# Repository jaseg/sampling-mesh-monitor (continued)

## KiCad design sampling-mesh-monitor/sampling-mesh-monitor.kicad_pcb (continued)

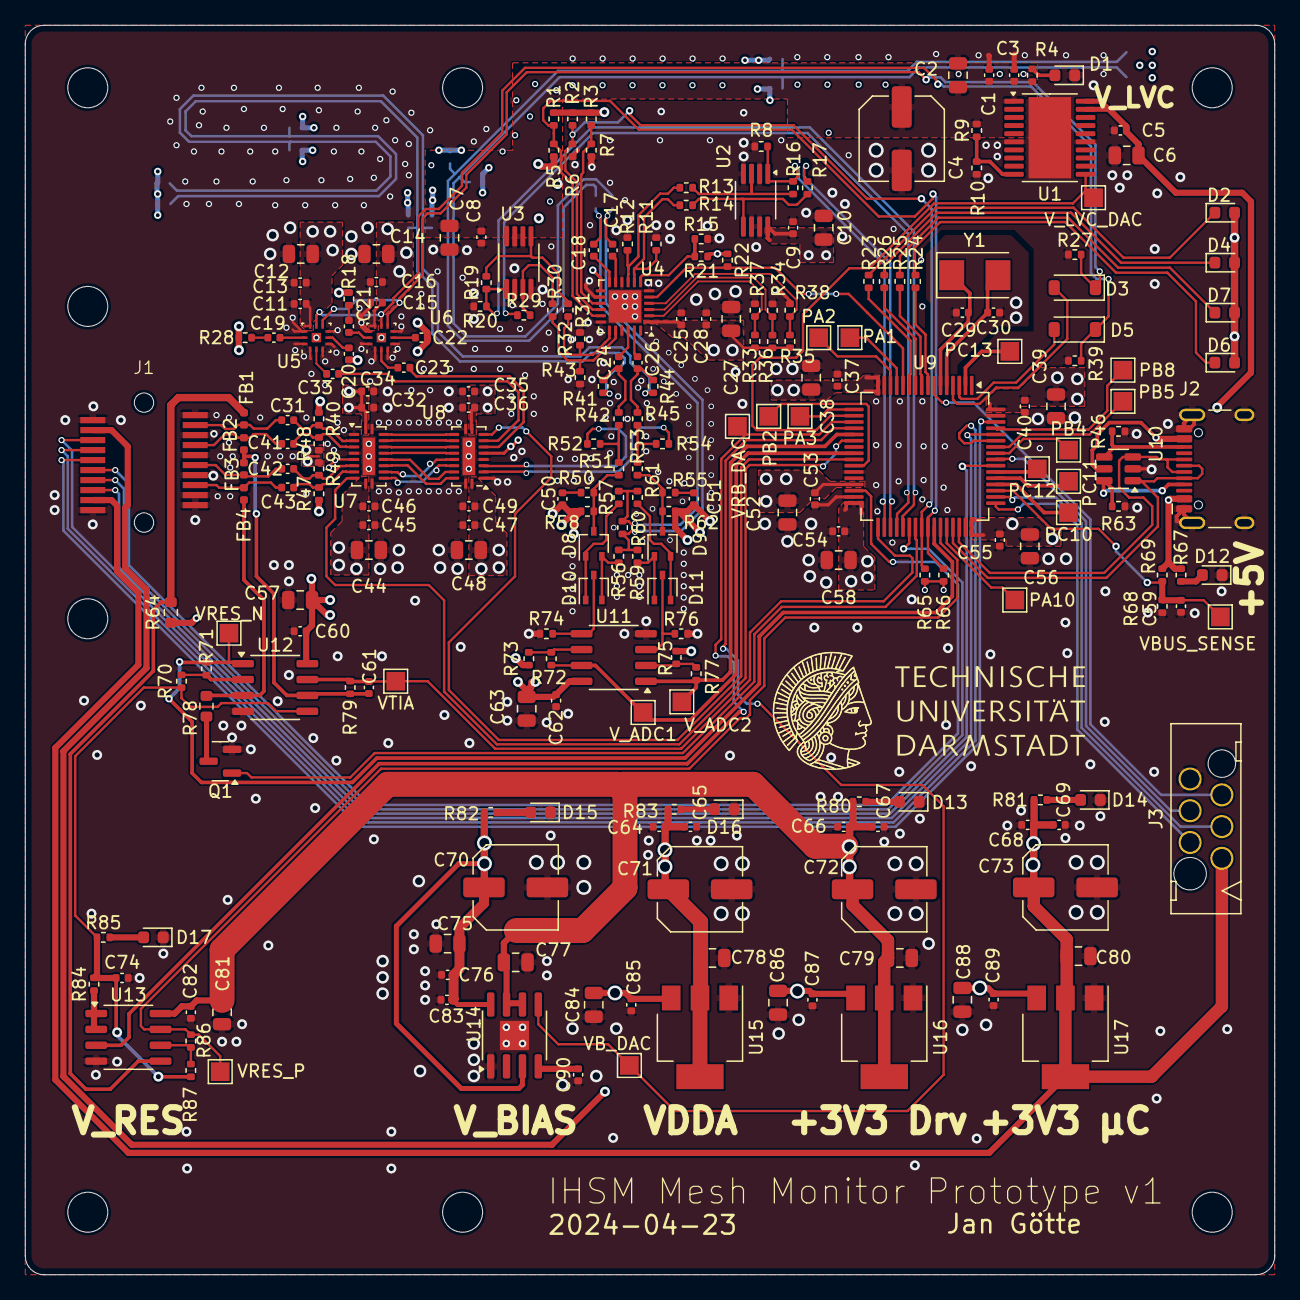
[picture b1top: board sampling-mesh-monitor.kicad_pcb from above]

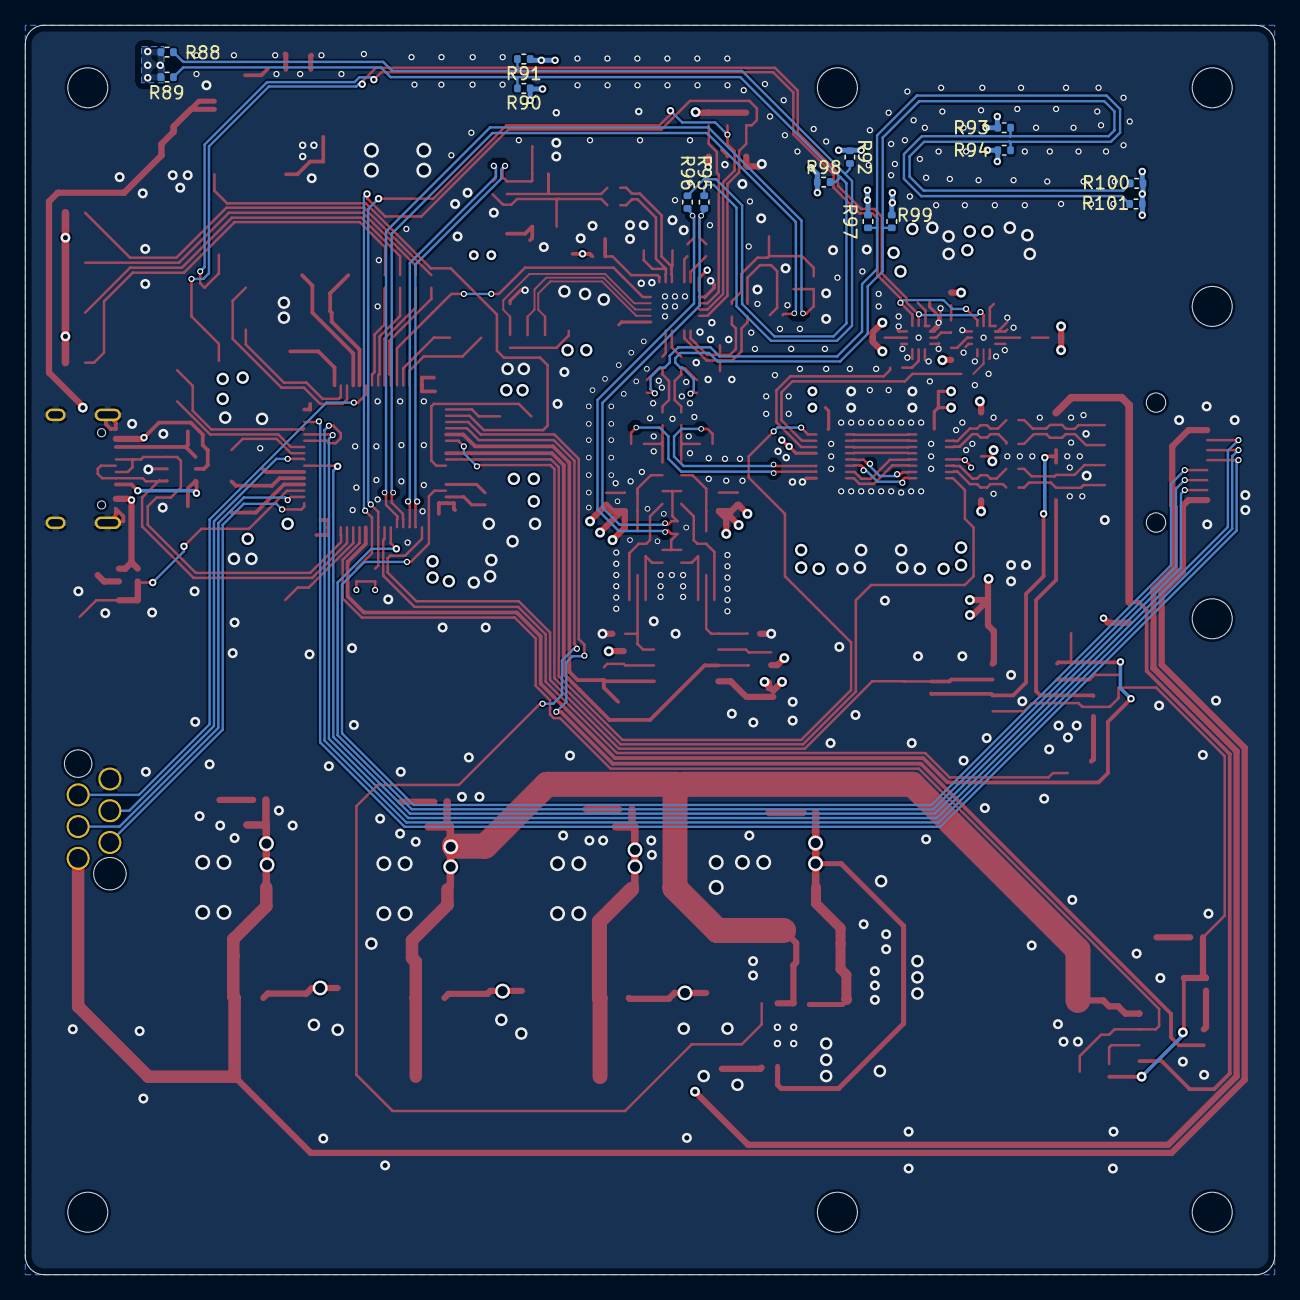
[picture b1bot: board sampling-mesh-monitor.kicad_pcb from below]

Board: 15 copper layers, 100.0 x 100.0 mm, 264 parts (14 on the bottom side), 150 nets.

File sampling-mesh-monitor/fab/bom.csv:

Comment,Designator,Footprint,LCSC
22k,"R68,R73,R75",Resistor_SMD:R_0402_1005Metric,C25768
47u,"C4,C70,C71,C72,C73",Capacitor_SMD:C_Elec_6.3x7.7,C88810
10n,"C3,C11,C15,C17,C18,C19,C20,C21,C22,C23,C24,C25,C26,C31,C32,C33,C36,C41,C42,C43,C46,C49,C65,C67,C69,C74,C76,C90",Capacitor_SMD:C_0402_1005Metric,C15195 
1k,"R4,R23,R24,R25,R26,R67,R80,R81,R82,R83,R85,R87",Resistor_SMD:R_0402_1005Metric,C11702 
45,"R18,R28,R58,R62",Resistor_SMD:R_0402_1005Metric,C327342
3k3,"R27,R39,R65,R66",Resistor_SMD:R_0402_1005Metric,C25890
1u,"C2,C6,C7,C10,C12,C14,C27,C38,C39,C44,C48,C52,C56,C57,C58,C63,C75,C77,C78,C79,C80,C81,C84,C86,C88",Capacitor_SMD:C_0805_2012Metric,C28323
0,"R9,R13,R14,R30,R31,R41,R44,R95,R96",Resistor_SMD:R_0402_1005Metric,C17168 
USBLC6-4SC6,U10,Package_TO_SOT_SMD:SOT-23-6,C558419
AO3400A,Q1,Package_TO_SOT_SMD:SOT-23,C20917
10k,"R40,R47,R48,R49,R70",Resistor_SMD:R_0402_1005Metric,C2654005
100n,"C1,C5,C8,C9,C13,C16,C28,C34,C35,C37,C40,C45,C47,C53,C54,C55,C59,C60,C62,C64,C66,C68,C82,C83,C85,C87,C89",Capacitor_SMD:C_0402_1005Metric,C307331
75,"R8,R11,R12,R20,R32,R43",Resistor_SMD:R_0402_1005Metric,C25133
BLM15HD102SN1D,"FB1,FB2,FB3,FB4",Inductor_SMD:L_0402_1005Metric,C21516
91,"R56,R57,R59,R61",Resistor_SMD:R_0402_1005Metric,C4071412
1N4148W,"D3,D5",Diode_SMD:D_SOD-123,C81598
47k,"R71,R72,R77,R86",Resistor_SMD:R_0402_1005Metric,C25792
PTN36241B,U4,Package_DFN_QFN:QFN-24-1EP_4x4mm_P0.5mm_EP2.6x2.6mm,C2675242
0603 white,"D1,D2,D4,D6,D7,D12,D13,D14,D15,D16,D17",LED_SMD:LED_0603_1608Metric,C2290
SKYA21003,"U5,U6",footprints:QFN-12_EP_2x2_Pitch0.5mm,C141440
74LVC2G157,"U2,U3",Package_SO:MSOP-8_3x3mm_P0.65mm,C78048 
30,"R42,R45,R51,R52,R53,R54",Resistor_SMD:R_0402_1005Metric,C138007
100,R84,Resistor_SMD:R_0402_1005Metric,C25076
20p,"C29,C30",Capacitor_SMD:C_0402_1005Metric,C1554
OPA1656,"U11,U12,U13",Package_SO:SO-8_3.9x4.9mm_P1.27mm,C1849431
BAT17-04W,"D8,D9,D10,D11",Package_TO_SOT_SMD:SOT-323_SC-70,C503474
AMS1117-3.3,"U15,U16,U17",Package_TO_SOT_SMD:SOT-223-3_TabPin2,C6186
5k1,"R46,R63",Resistor_SMD:R_0402_1005Metric,C25905
47,"R64,R78",Resistor_SMD:R_0603_1608Metric,C23182
TMUXHS4212,"U7,U8",Package_DFN_QFN:DHVQFN-20-1EP_2.5x4.5mm_P0.5mm_EP1x3mm,C3656912
1M,"R74,R76,R79",Resistor_SMD:R_0402_1005Metric,C138033
USB_C_Receptacle_USB2.0,J2,Connector_USB:USB_C_Receptacle_HCTL_HC-TYPE-C-16P-01A,C2988369
8MHz/20p,Y1,Crystal:Crystal_SMD_5032-2Pin_5.0x3.2mm,C115962
SFP+,J1,footprints:HCTL_HC-SFP-20P_C2897291,C2897291
100k,R69,Resistor_SMD:R_0402_1005Metric,C25741
STM32G474RBTx,U9,Package_QFP:LQFP-64_10x10mm_P0.5mm,C529413
TPS7B4253QPWPRQ1,U1,Package_SO:HTSSOP-20-1EP_4.4x6.5mm_P0.65mm_EP3.4x6.5mm_Mask2.4x3.7mm,C2879376
LP2998,U14,footprints:SOIC-8-1EP_3.9x4.9mm_P1.27mm_EP2.34x2.34mm,C181400

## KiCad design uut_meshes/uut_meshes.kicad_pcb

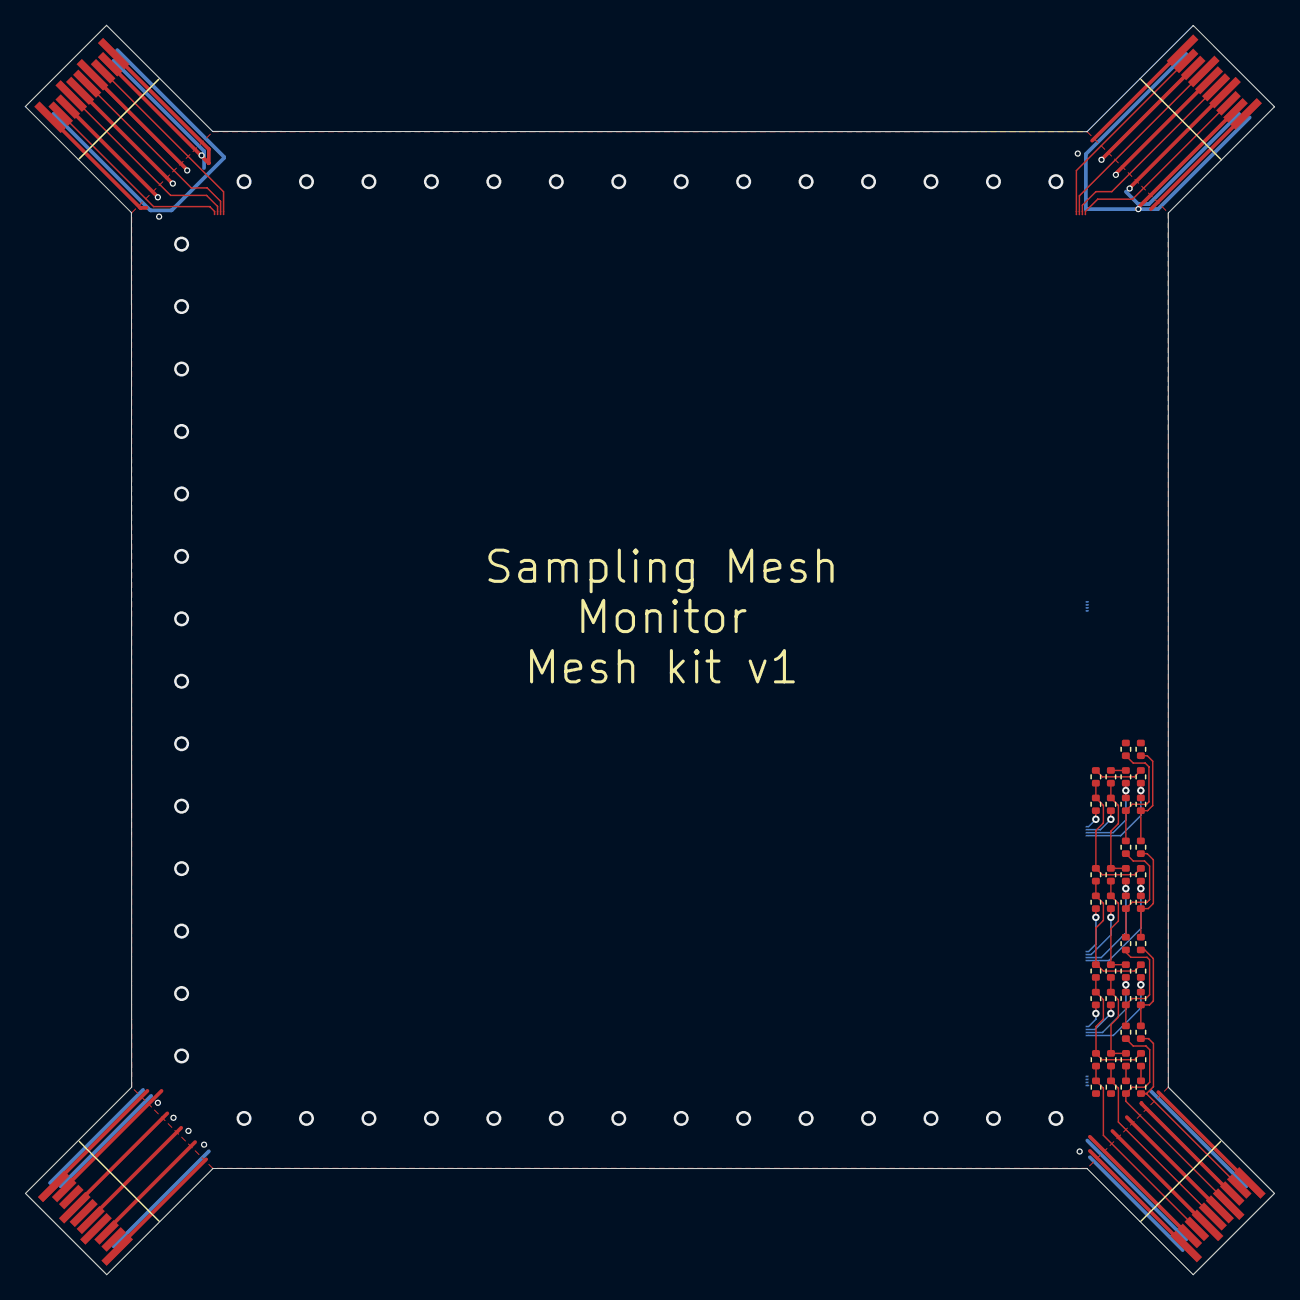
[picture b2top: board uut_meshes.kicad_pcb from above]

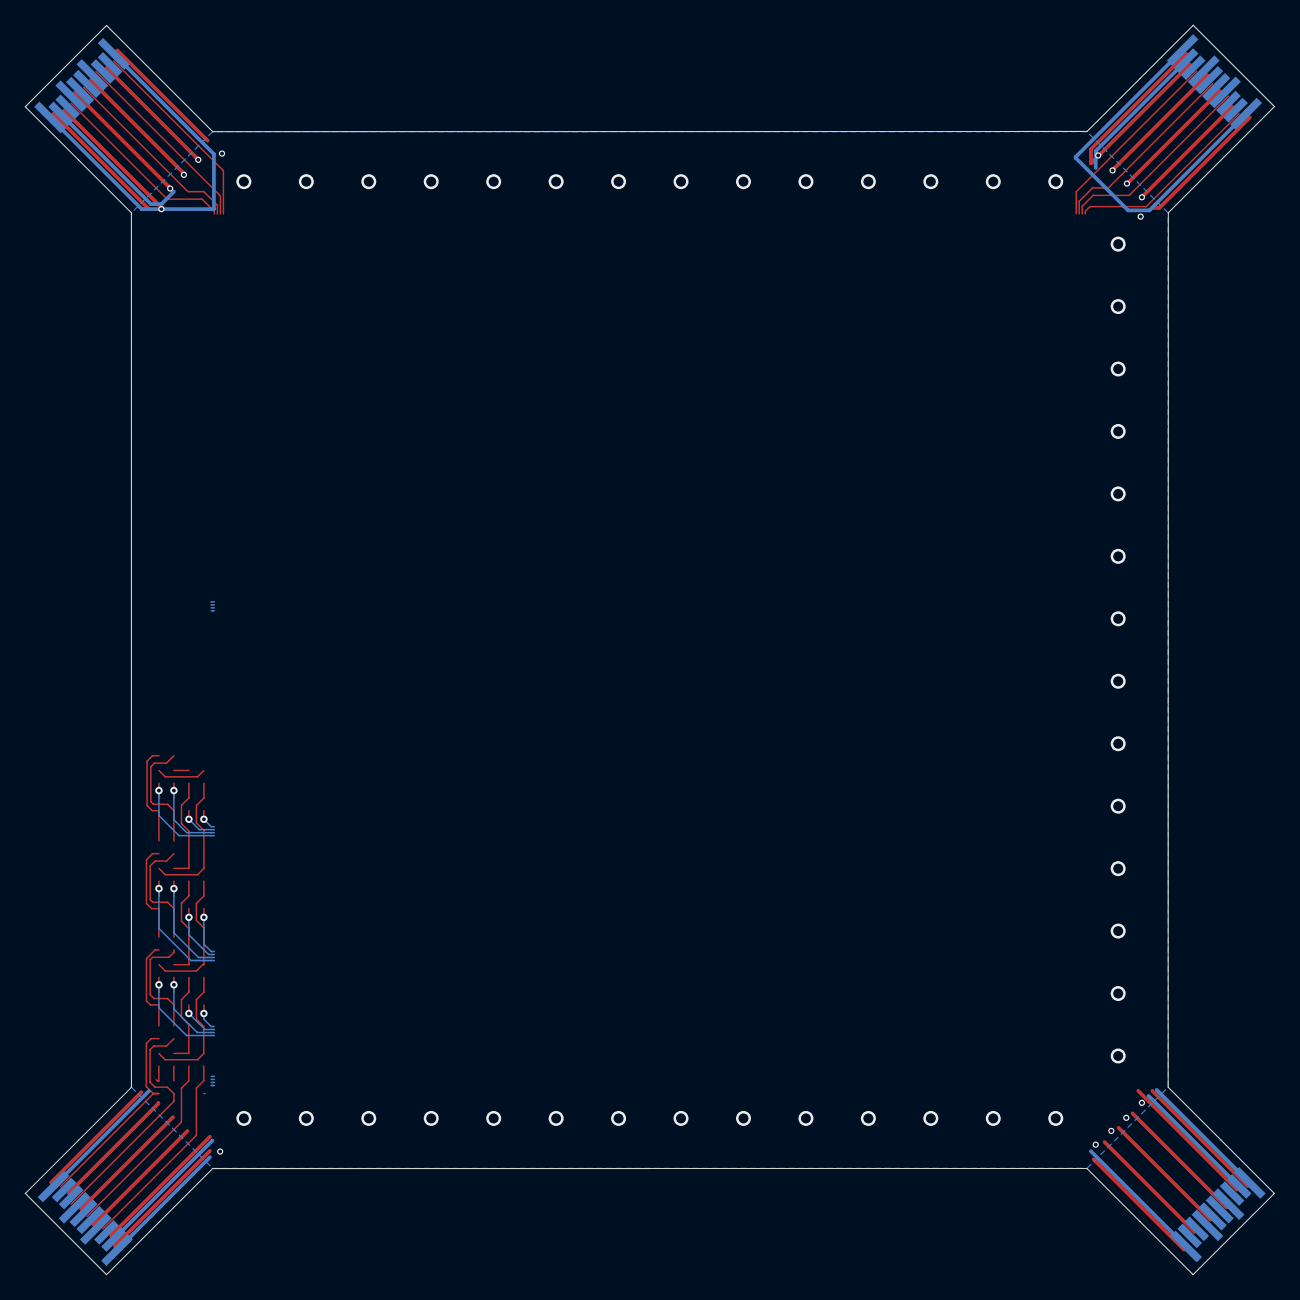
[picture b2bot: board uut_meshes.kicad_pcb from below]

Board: 4 copper layers, 100.0 x 100.0 mm, 51 parts (5 on the bottom side), 57 nets.

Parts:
J1, J2, J3, J4: Conn_02x10_Counter_Clockwise; sfp_edge_connector_male
J5, J6, J7, J9, J10, J11, J12: Conn_02x04_Top_Bottom; MeshAnchor_2W_T0.120mm_S0.120mm
R1, R2, R3, R4, R5, R6, R7, R8, R9, R10, R11, R12, R13, R14, R15, R16, R17, R18, R19, R20, R21, R22, R23, R24, R25, R26, R27, R28, R29, R30, R31, R32, R33, R34, R35, R36, R37, R38, R39, R40: 0; R_0402_1005Metric

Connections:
GND: J1.1, J1.9, J1.10, J1.11, J1.12, J1.14, J1.16, J1.18, J1.20, J2.1, J2.9, J2.10, J2.11, J2.12, J2.14, J2.16, J2.18, J2.20, J3.1, J3.9, J3.10, J3.11, J3.12, J3.14, J3.16, J3.18, J3.20, J4.1, J4.9, J4.10, J4.11, J4.12, J4.14, J4.16, J4.18, J4.20
unnamed: J1.13, J6.1
unnamed: J1.15, J6.2
unnamed: J1.17, J6.3
unnamed: J1.19, J6.4
unnamed: J2.13, R2.2, R5.2
unnamed: J2.15, R1.2, R6.2
unnamed: J2.17, R3.2, R10.2
unnamed: J2.19, R4.2, R9.2
unnamed: J4.13, J5.1
unnamed: J4.15, J5.2
unnamed: J4.17, J5.3
unnamed: J4.19, J5.4
unnamed: J5.5, J5.8
unnamed: J5.6, J5.7
unnamed: J6.5, J6.8
unnamed: J6.6, J6.7
unnamed: J7.1, R2.1
unnamed: J7.2, R1.1
unnamed: J7.3, R3.1, R8.2
unnamed: J7.4, R4.1, R7.2
unnamed: J7.5, J7.8
unnamed: J7.6, J7.7
unnamed: J9.1, R11.1
unnamed: J9.2, R12.1
unnamed: J9.3, R13.1, R19.2
unnamed: J9.4, R14.1, R20.2
unnamed: J9.5, J9.8
unnamed: J9.6, J9.7
unnamed: J10.1, R21.1
unnamed: J10.2, R22.1
unnamed: J10.3, R23.1, R29.2
unnamed: J10.4, R24.1, R30.2
unnamed: J10.5, J10.8
unnamed: J10.6, J10.7
unnamed: J11.1, R31.1
unnamed: J11.2, R32.1
unnamed: J11.3, R33.1, R39.2
unnamed: J11.4, R34.1, R40.2
unnamed: J11.5, J11.8
unnamed: J11.6, J11.7
unnamed: J12.5, J12.8
unnamed: J12.6, J12.7
unnamed: R10.1, R13.2, R16.2
unnamed: R5.1, R7.1, R11.2, R18.2
unnamed: R6.1, R8.1, R12.2, R17.2
unnamed: R9.1, R14.2, R15.2
unnamed: R15.1, R24.2, R25.2
unnamed: R16.1, R23.2, R26.2
unnamed: R17.1, R19.1, R22.2, R27.2
unnamed: R18.1, R20.1, R21.2, R28.2
unnamed: R25.1, R34.2, R35.2
unnamed: R26.1, R33.2, R36.2
unnamed: R27.1, R29.1, R32.2, R37.2
unnamed: R28.1, R30.1, R31.2, R38.2
unnamed: R37.1, R39.1
unnamed: R38.1, R40.1

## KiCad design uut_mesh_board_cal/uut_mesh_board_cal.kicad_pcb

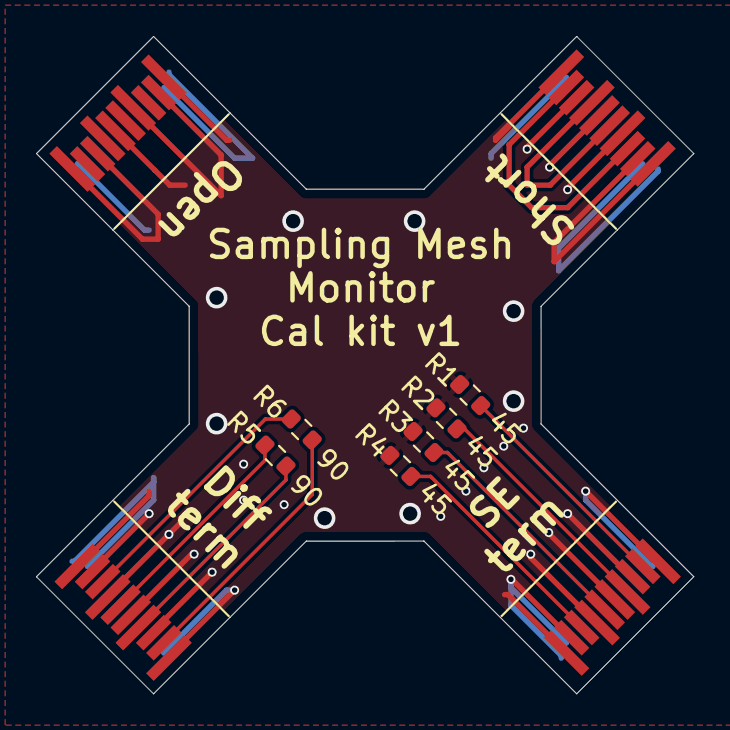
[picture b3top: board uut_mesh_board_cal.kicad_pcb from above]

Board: 2 copper layers, 36.5 x 36.5 mm, 11 parts (1 on the bottom side), 11 nets.

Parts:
J1, J2, J3, J4: Conn_02x10_Counter_Clockwise; sfp_edge_connector_male
R1, R2, R3, R4: 45; R_0603_1608Metric
R5, R6: 90; R_0603_1608Metric
logo_tu_darmstadt_15.0mm: G*****; logo_tu_darmstadt_15.0mm

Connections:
GND: J1.1, J1.9, J1.10, J1.11, J1.12, J1.14, J1.16, J1.18, J1.20, J2.1, J2.9, J2.10, J2.11, J2.12, J2.14, J2.16, J2.18, J2.20, J3.1, J3.9, J3.10, J3.11, J3.12, J3.14, J3.16, J3.18, J3.20, J4.1, J4.9, J4.10, J4.11, J4.12, J4.14, J4.16, J4.18, J4.20, R1.1, R2.1, R3.1, R4.1
unnamed: J1.13, J1.19
unnamed: J1.15, J1.17
unnamed: J2.13, R4.2
unnamed: J2.15, R3.2
unnamed: J2.17, R2.2
unnamed: J2.19, R1.2
unnamed: J3.13, R6.1
unnamed: J3.15, R5.1
unnamed: J3.17, R5.2
unnamed: J3.19, R6.2

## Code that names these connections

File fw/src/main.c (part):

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                    AFRH(14, 0) | /* SWCLK */
                    AFRH(10, 13); /* HRTIM1 Channel B1 */
    GPIOA->OSPEEDR = 0xffffffff;
    GPIOA->BRR = (1<<0); /* Clear DRV_CEN */

    /* GPIOB: 
     *  0 -  V_ADC1 -> ADC1 CH15
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
    GPIOB->MODER = ANALOG(0) | OUT(1) | IN(2) | AF(3) | AF(4) | IN(5) | IN(6) | IN(7) | OUT(8) | IN(9) | IN(10) |
        ANALOG(11) | AF(12) | IN(13) | IN(14) | AF(15);
    GPIOB->AFR[0] = AFRL( 3, 0)  | /* SWO */
                    AFRL( 4, 1);   /* TIM16 CH1 */
    GPIOB->AFR[1] = AFRH(12, 13) | /* HRTIM1 Channel C1 */
                    AFRH(13, 13) | /* HRTIM1 Channel C2 */
                    AFRH(14, 13) | /* HRTIM1 Channel D1 */
                    AFRH(15, 13);  /* HRTIM1 Channel D2 */
    GPIOB->OSPEEDR = 0xffffffff;
    GPIOB->BSRR = (1<<1); /* Set MESH_FLIP_N, leave MESH_FLIP reset below. These two must be complementary. */

    /* GPIOC:
     *  0 -  LED1
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
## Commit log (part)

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2024-04-24 Initial commmit
2024-04-24 PCB almost finished
2024-04-24 Reannotate reference designators by PCB location
2024-04-24 Add cal kit UUT
2024-04-24 uut/cal kit: Add version number
2024-04-24 uut/mesh: Add mesh uut
2024-04-25 Mesh test board WIP
2024-04-25 meshes WIP
2024-07-22 Add fw skeleton
2024-07-22 redriver bringup WIP
2024-11-18 Get the ADCs converting
2024-11-19 Add live measurement plot
2024-11-20 Add clock documentation
2024-11-20 We get first, very rough sampled measurements
2024-11-20 Speed up display
2024-11-22 straighten out HRTIM triggering
2024-11-22 Improved channel 1 sampling
2024-11-22 I2C wasn't working, with pin-strapped driver config we now get some *very* spicy edges it seems
    This commit also scales the web UI plots' X axis in ns and Y axis in V.
2024-11-23 Add todos to board schematic
2024-11-23 Move stimulus instead of sampling pulse, eliminates ADC alignment issue
    The ADC can only trigger on whole clock pulses, so when we move the
    sampling pulse in fractional increments, the relative alignment of the
    ADC's sampling phase w.r.t. sampling pulse moves around +/-0.5 clock
    periods. Since our opamps ring a bit, that leads to an artifact in the
    measurements with a period of 32 samples (one whole clock pulse). Moving
    the stimulus pulse instead fixes this issue, as now the alignment
2024-11-23 Decrease oversampling to increase update rate
2024-11-23 Something weird is happening with the hrtim master period
    This new value gives much cleaner curves. I suspect that either we have
    some issue with ADC sampling not being precise due to clock domain
    crossings, or this is just interference and the new period hits a sweet
    spot that is coherent with this interference.
2024-11-25 Extend remote control both ways
2024-11-25 make sampling phase and width remotely configurable
2024-11-26 It's roughly doing what it's supposed to do now.
    We have mystery oscillations.
2024-11-26 re-enable oversampling
2024-12-02 Properly tuned double-edge sampling
2024-12-02 Make oversampling configurable
2024-12-11 Add paper scaffold
2024-12-14 Paper WIP
2025-01-28 Add input clamping diodes
2025-01-29 Add spectrum measurement results
2025-01-29 Initial analysis of measurements
2025-01-29 Finished preliminary bandwidth analysis.
2025-01-29 Add second risetime calculation
2025-02-07 Undo temporary spectrum measurement changes
2025-02-07 Update fw/interface to add variance data
2025-02-07 fw: Fix aliasing issue, improve web IF
2025-03-10 paper: Text on mesh related work and circuit design
2025-03-11 Fix build
2025-03-27 Add capture data for all chips except ONET
2025-03-27 Add repeated measurements for broken board and for risetime tuning
2025-03-27 Add risetime notebook
2025-03-27 Improve plots
2025-03-28 Add exported risetime graph
2025-03-28 Update risetime plots with thresholds
2025-03-28 Update paper
2025-03-28 Add more plots
2025-03-31 Update probe plot
2025-03-31 Improve probe shape plots
2025-04-02 Re-do length measurements with cliplines
2025-04-02 Fix 74LVC length plot offset
2025-04-02 Add new manipulation experiments
2025-04-02 Fix javascript data corruption issue and re-do manipulation measurements
2025-04-02 Add mesh length calculation and visualization tool
2025-04-02 Run exports
2025-04-02 Add speed of light calculation
2025-04-02 Enable spectrum measurement mode
    Revert "Undo temporary spectrum measurement changes"
    This reverts commit a2d95a324ae03bfd388dcb72b759d3f698038c32.
2025-04-02 Fix legends not showing up in some plots
2025-04-03 Add new spectrum measurements
2025-04-03 Update trace plot alignment
2025-04-03 Update spectral analysis, increase test fw gen frequency
2025-04-03 Add missing spectrum data
2025-04-03 Add spectrum plots, looking good!
2025-04-04 paper: Add more pictures
2025-04-04 Add more sources
2025-04-04 More related work
2025-04-04 Paper: improve structure
2025-04-05 Make risetime numbers comparable by using consistent thresholds
2025-04-05 Fix risetime calculation
2025-04-05 Update risetime notebook
2025-04-07 A lot more text
2025-04-07 Try out ACM style
2025-04-08 Add block diagram draft
2025-04-08 Block diagram WIP
2025-04-08 Revert "Try out ACM style"
    This reverts commit a66f6a878fbc9b81ae797ac7e25629ac12bb1123.
2025-04-08 Add block diagram pdf export
2025-04-08 Rework WIP
2025-04-08 Review pass mostly done, first half primarily
2025-04-08 Remove git repo URL
2025-04-09 Proof work
2025-04-09 Revert "Enable spectrum measurement mode"
    This reverts commit f335d96c4f549d39098c66153fe3a72ebb055d40.
2025-04-09 Paper done, add one more attack
2025-04-09 Move some photos to the appendix
2025-04-09 Add missing figure source files
2025-04-09 Small fixes
2025-04-10 Fix some small stuff
2025-04-10 Update abstract
2025-04-10 Fix up patent citations
2025-04-10 Clean up duplicate fields in printed bibliography
2025-04-10 Remove redundant macro
2025-04-11 Add tobi's comments
2025-04-11 Paper rework WIP
2025-04-14 Multiple wording improvements
2025-04-14 Fix paper email
2025-04-14 Some spelling fixes
2025-04-15 Spellcheck WIP
2025-04-15 Finish spell checking pass
2025-04-15 Fix rise time plots
2025-04-15 Add missing notebook
2025-04-17 Remove patenting mention
2025-06-02 Add classification/correlation calculations for rebuttal
2025-06-17 Add new mesh coupons
2025-06-23 Add new measurement recording infrastructure
2025-06-23 Last wording fixes
2025-06-23 Add comments, fix sampling bug, add tdp0604 serial
2025-06-24 Try to re-focus the input field after scanning
2025-06-27 Add specimen serial qr gen and first measurements
2025-06-27 Add TDP0604 measurements
2025-06-30 Add classifier notebook
2025-06-30 Record 2025-06-30 mods
2025-07-01 Clean up live plot interface
2025-07-02 Disable auto-download for now
2025-07-02 data: add 25-07-01-01 batch
2025-07-02 data: add batch 25-07-02-01
2025-07-02 Work on baseline classifier
2025-07-02 Notebooks WIP
2025-07-02 Add interleaved p0.3 measurements
2025-07-02 Add multi trace viewer notebook
2025-07-02 More data analysis
2025-07-02 data: add interleaved probing batch
2025-07-02 data: add 25-07-02-04 batch
2025-07-02 data: add hot mesh batch
2025-07-02 data: add missing hot baselines
2025-07-02 Add elevated temperature data
2025-07-02 data: add more repeat measurements
2025-07-02 Add long-term (~3h) drift measurement
2025-07-03 Fix bug leading to invalid cal measurements
2025-07-03 Add tempco figures
2025-07-03 Add publication-ready plots
2025-07-07 Add 2025-07-07-01 attack batch
2025-07-07 Lots of new plots
2025-07-08 Add 2025-07-08-01 environmental batch
2025-07-08 Update notebook
2025-07-08 Add loop patch attack batch
2025-07-08 Add soldering iron probe run
2025-07-08 Add wire probe batch
2025-07-08 Add homeoffice environmental batch
2025-07-08 Add lots of new plots
2025-07-09 Add forest environment batch
2025-07-09 Add forest environment plots
2025-07-09 Update forest interleave plot to only use batch size of 10
2025-07-09 Add labels to environment plots
2025-07-09 Fix CER/error rate calculation
2025-07-09 Add legend to CDF plots
2025-07-09 src/main.c: Add more comments
2025-07-09 Add anonymized gerber and PDF schematic exports
2025-07-09 Add forest setup pics
2025-07-09 Add new measurements of loop patches using both drivers
2025-07-09 Update all figures, include traces of calculated results
2025-07-09 Add repeat loop patch measurement batch
2025-07-09 Add repeat loop patch run plots
2025-07-09 Improve loop patch classifier performance by enabling smoothing
2025-07-09 Fiddle with plots
2025-07-10 Add triangle-delta classifier improvement, and large-scale plot
2025-07-10 Improve larger covariance plots
2025-07-11 Add 25-07-11-01 interleave copy batch
2025-07-11 Add distinguish copies run plots
2025-07-11 Add interleaved loop patch batch
2025-07-11 Add interleaved before/after patch batch
2025-07-11 fw/web: Add trigger mode
2025-07-11 Add short within trace interleaved batch
2025-07-14 Cut down a bunch of stuff, make space for majR measurements
2025-07-14 majR WIP
2025-07-15 Color figure captions
2025-07-15 Update source info
2025-07-15 Change highlight color scheme to red/blue and add note to the title page
2025-07-16 majR: final changes
2025-08-29 Add revision letter
2025-08-30 Revision letter draft
2025-09-01 Update revision letter
2025-09-28 Minor revision WIP
2025-09-29 Update all CER values with ones derived from the distributions
2025-09-29 adjust CER explanation
2025-09-30 Add missing citations
2025-09-30 Minor revision draft
2025-09-30 Include Konrad's feedback
2025-10-02 Add final camera ready export
2025-10-02 Fix repo URL
2025-10-20 Fix URL formatting
2025-10-21 Typo fix
2025-10-27 Add fabrication exports
2025-10-27 Add missing gerbers
2025-10-27 Repo re-org for artifact submission
2025-10-27 Add README
2025-10-27 README: Add blog link and header photo
2025-10-27 Document jupyter notebooks for artifact release
2025-10-27 README: Convert LaTeX in abstract to unicode
2025-10-27 README: Fix schematics path
2025-10-27 README: Update with instructions for replication
2025-10-27 README: Describe data format better
2025-11-11 Add LICENSE
2025-11-20 Add analysis of scope measurements
2025-12-02 Add raw scope data
2025-12-02 Update scope pulse plots for thesis
2026-01-13 Add detailed requirements for notebooks and analysis scripts
2026-01-13 Fix remaining runtime errors in jupyter notebooks
2026-01-14 Add version numbers to requirements files
2026-01-14 Add ipympl notebook requirement
2026-01-14 Update README with more board info
2026-01-24 Add jupyterlab to requirements.txt
